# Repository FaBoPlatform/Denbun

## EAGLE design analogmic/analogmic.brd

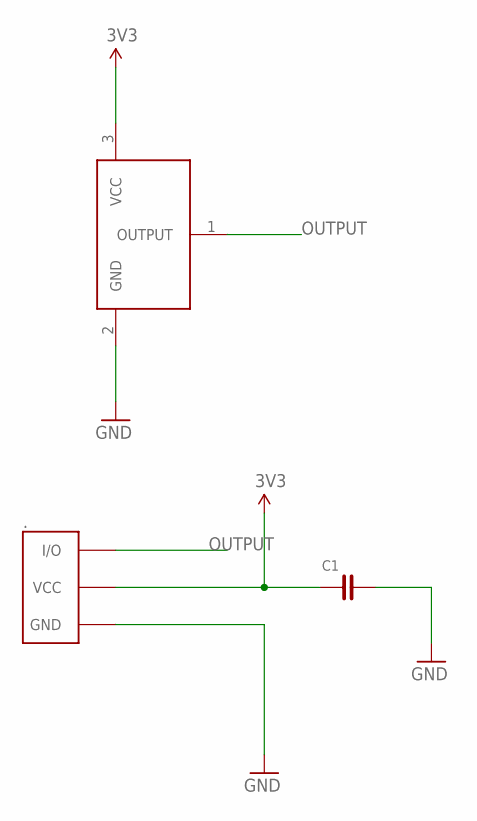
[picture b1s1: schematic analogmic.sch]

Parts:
.: FABO_BRICK_3PIN-S03B-PASK-2; FABO_BRICK_3PIN_S03B-PASK-2
C1: CAPACITOR-0603; 0603
ICS-40310: ANALOG-MIC; ICS40310

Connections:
3V3: ..VCC, C1.1, ICS-40310.3 (VCC)
GND: ..GND, C1.2, ICS-40310.2 (GND)
OUTPUT: ..I/O, ICS-40310.1 (OUTPUT)

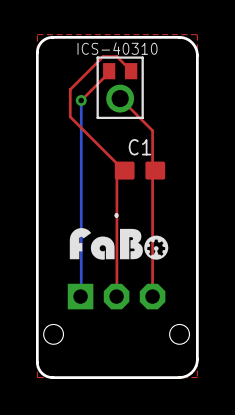
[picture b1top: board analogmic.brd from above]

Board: 2 copper layers, 8.9 x 18.9 mm, 4 parts (0 on the bottom side), 3 nets.

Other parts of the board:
U$2: LOGO_FABO_S

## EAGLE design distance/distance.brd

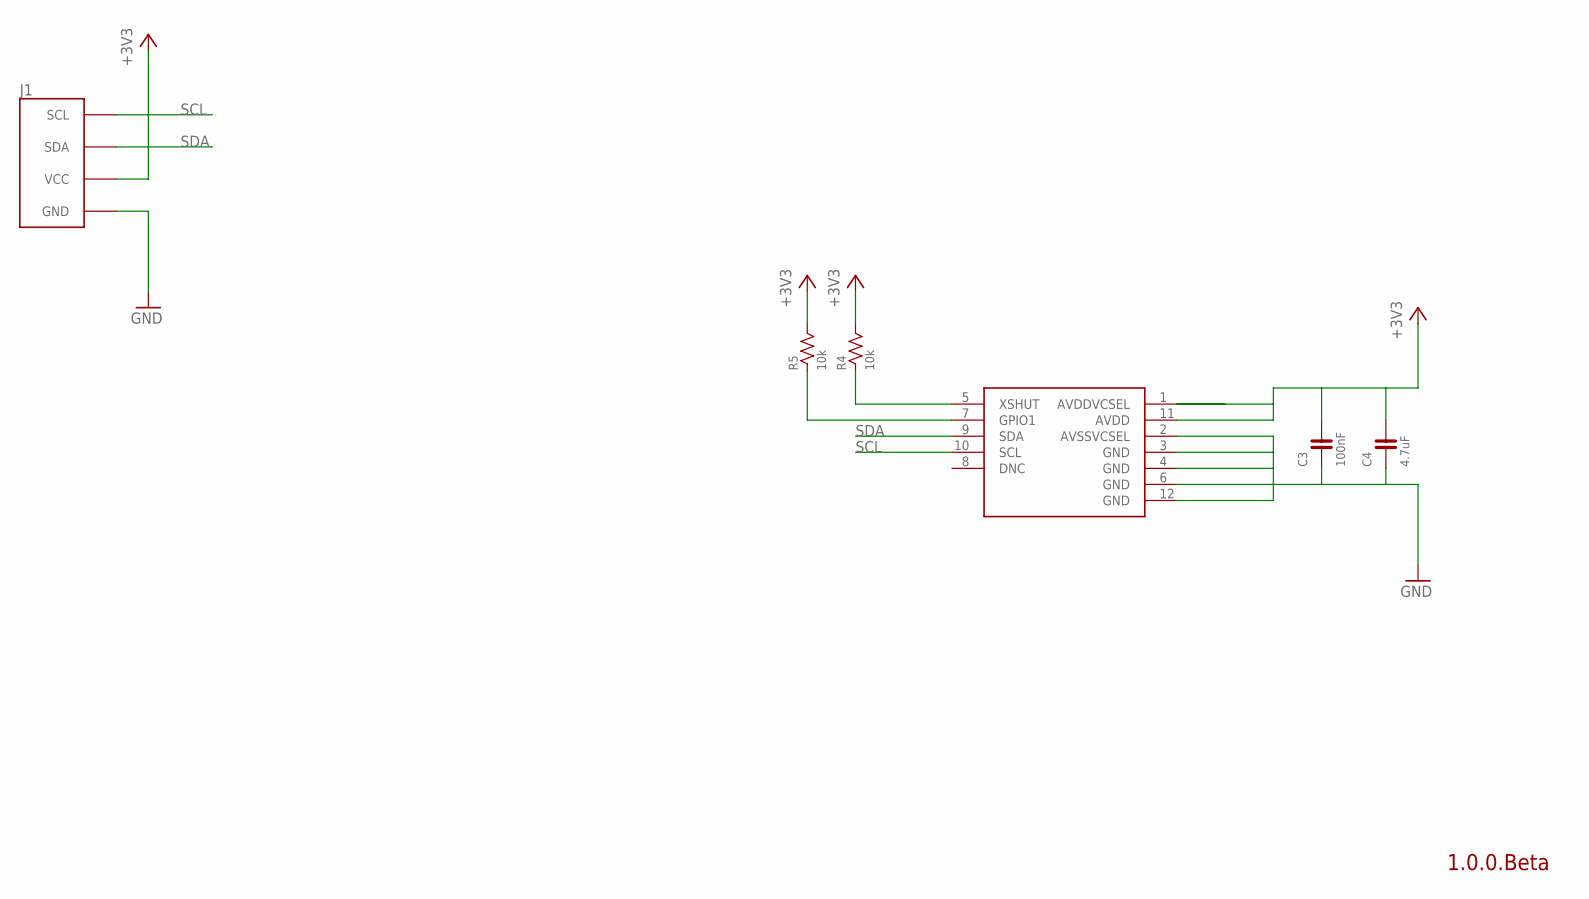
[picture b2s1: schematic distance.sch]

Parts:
C3: 100nF; 0603
C4: 4.7uF; 0603
J1: FABO_BRICK_I2C-B04B-PASK-1_SILK_BOTTOM; FABO_BRICK_I2C_B04B-PASK-1_SILK_BOTTOM
R4, R5: 10k; 0603
VL1: ST-VL53L0XVL53; ST-VL53L0X

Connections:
+3V3: C3.2, C4.2, J1.VCC, R4.2, R5.2, VL1.1 (AVDDVCSEL), VL1.11 (AVDD)
GND: C3.1, C4.1, J1.GND, VL1.2 (AVSSVCSEL), VL1.3 (GND), VL1.4 (GND), VL1.6 (GND), VL1.12 (GND)
unnamed: R4.1, VL1.5 (XSHUT)
unnamed: R5.1, VL1.7 (GPIO1)
SCL: J1.SCL, VL1.10 (SCL)
SDA: J1.SDA, VL1.9 (SDA)

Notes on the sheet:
1.0.0.Beta

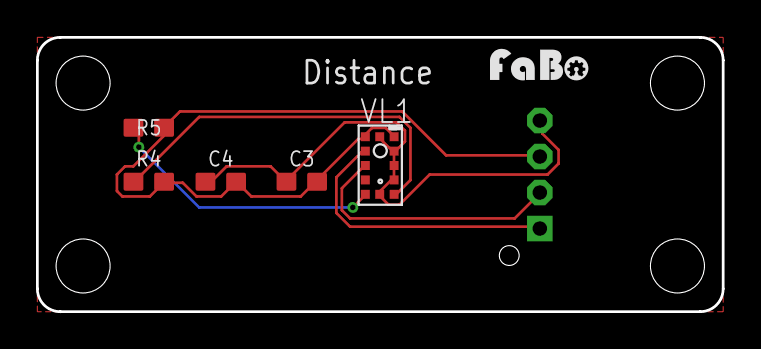
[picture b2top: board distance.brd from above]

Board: 2 copper layers, 38.1 x 15.2 mm, 7 parts (0 on the bottom side), 6 nets.

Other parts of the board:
U$2: LOGO_FABO_S

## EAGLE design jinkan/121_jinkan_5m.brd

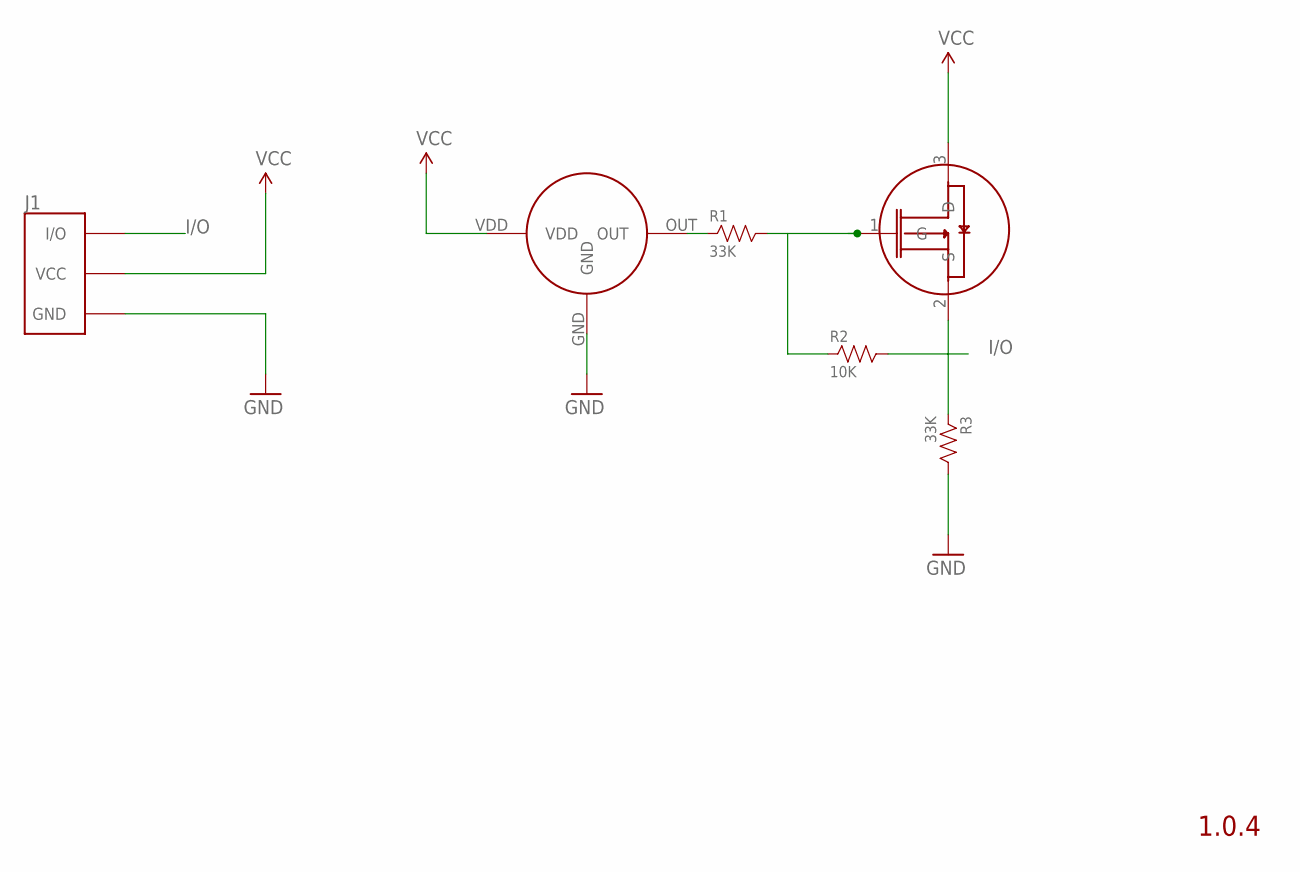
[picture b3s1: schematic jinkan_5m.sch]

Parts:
J1: FABO_BRICK_3PIN-B03-PASK-1_SILK_BOTTOM; FABO_BRICK_3PIN_B03B-PASK-1_SILK_BOTTOM
R1, R3: 33K; 0603
R2: 10K; 0603
SW1: FAIRCHILD-FDN338; SOT23
U$4: EKBM; EKMB

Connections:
GND: J1.GND, R3.2, U$4.GND
I/O: J1.I/O, R2.2, R3.1, SW1.2 (S)
unnamed: R1.1, U$4.OUT
unnamed: R1.2, R2.1, SW1.1 (G)
VCC: J1.VCC, SW1.3 (D), U$4.VDD

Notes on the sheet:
1.0.4

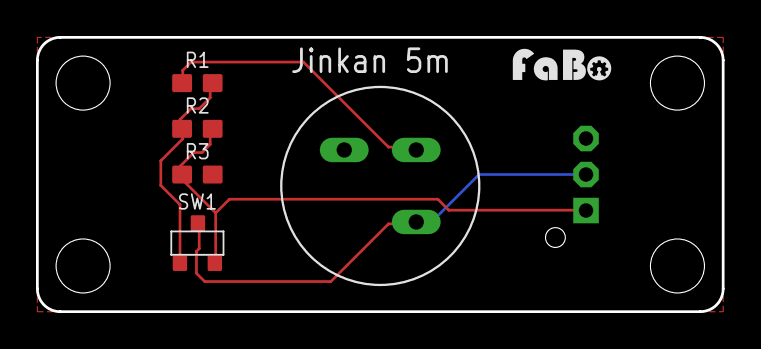
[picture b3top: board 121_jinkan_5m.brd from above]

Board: 2 copper layers, 38.1 x 15.2 mm, 7 parts (0 on the bottom side), 5 nets.

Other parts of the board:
U$2: LOGO_FABO_S

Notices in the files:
parts and their libraries:
FaBo-Capacitor: Released under the Creative Commons Attribution-ShareAlike 4.0 License
https://creativecommons.org/licenses/by-sa/4.0
FaBo-etc: Released under the Creative Commons
